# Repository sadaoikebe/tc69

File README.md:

# TC69 静電容量親指シフト 65% キーボード

## 特徴

オープンソースの親指シフトキーボードです。

* 静電容量式
* QMK対応
* JLCPCBで作成したPCB
* 3Dプリントしたケース

## キーボード配列

* ANSI配列ベース
* 矢印キーあり
* 対応する親指シフトファームウェア [tc69 firmware](https://github.com/sadaoikebe/qmk_firmware/tree/capacitive)
* 親指シフト対応、親指キーB下割れ
* 親指キーに3u/2.75uのキーキャップを使用

<!--
["Esc\n\n~\n`","!\n1","@\n2","#\n3","$\n4","%\n5","^\n6","&\n7","*\n8","(\n9",")\n0","_\n-","+\n=",{w:2},"Backspace","Home"],
[{w:1.5},"Tab","Q","W","E","R","T","Y","U","I","O","P","{\n[","}\n]",{w:1.5},"|\n\\","PgUp"],
[{w:1.75},"Ctrl","A","S","D","F","G","H","J","K","L",":\n;","\"\n'",{w:2.25},"Enter","PgUp"],
[{w:2.25},"Shift","Z","X","C","V","B","N","M","<\n,",">\n.","?\n/",{w:1.75},"Shift","Up","End"],
[{a:7,w:1.25},"",{w:1.25},"",{w:1.25},"",{w:3},"3u 左親指",{w:2.75},"2.75u 右親指",{w:1.25},"",{w:1.25},"","","","",""],
-->

静電容量キーボードなので配列は固定で変えられません

# BOM

Item |ソース | 数量 |  備考
:--- | :--- | :--- | :---
TC69 PCBA | [JLCPCB PCBA](pcb/) | 1 |
オペアンプ AD8601ARTZ | AliEx/淘宝等 | 1 |
ロジック 74AHC1G04 | AliEx/淘宝等 | 1 |
ケース | [3D Printed](case/) | 1 | 
定位板 | [Laser Cut Brass](plate/) | 1 | t=1.5mm アクリルでも良いが割れやすい
ヒートセット M3x6mmx4.6mm | [AliEx/淘宝等](https://www.aliexpress.com/item/1005002288716120.html) | 8 | 長さは6mmでなくても良い
M3 円頭六角ボルト 6mm | | 8 |  
M2 低頭精密小ねじ M2*8mm FX-0280EB | [Wilco](https://wilco.jp/products/F/FX-EB.html#page3) | 12 |
クッション 2mm厚 x 60mm x 4mm | | 16 | Poron/EVAフォーム等
Seeed Xiao RP2040 | [Seeed Studio](https://www.seeedstudio.com/XIAO-RP2040-v1-0-p-5026.html) | 1 | 
NiZ プランジャーキット | [NiZ](https://www.nizkeyboard.com/products/2019-new-niz-ec-switch) | 1セット |
コニカルスプリング | [淘宝](https://item.taobao.com/item.htm?spm=a1z0d.6639537/tb.1997196601.4.194d74840XCdqh&id=616137021034) | 69 |
シリコンドーム | [NiZ](https://www.nizkeyboard.com/products/ec-silicone-domes-35g-45g-55g) | 1セット |
2u スタビライザー | AliEx/淘宝/自キ専門店等 | 5 | Plate Mount
3u スタビライザー | AliEx/淘宝/自キ専門店等 | 1 | Plate Mount
キーキャップ | AliEx/淘宝/自キ専門店等 | 1セット | 3u/2.75uの親指キーが必要

## 組み立て工程

1. 定位板はあらかじめM2タップを切る
2. PCBにXiao RP2040, オペアンプ, ロジックIC を取り付け
3. コニカルスプリングを並べてラバードームを乗せる
4. 定位板にハウジングを取り付け、プランジャーを通す
5. 定位板とPCBをM2*8ボルトで緊結する
6. PCBにクッションを貼る
7. ファームウェア書き込み
8. ケースに入れて完成

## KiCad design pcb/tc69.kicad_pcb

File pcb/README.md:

https://www.seeedstudio.com/blog/2020/04/23/use-seeeduino-xiao-in-kicad-pcb-design-like-a-components/

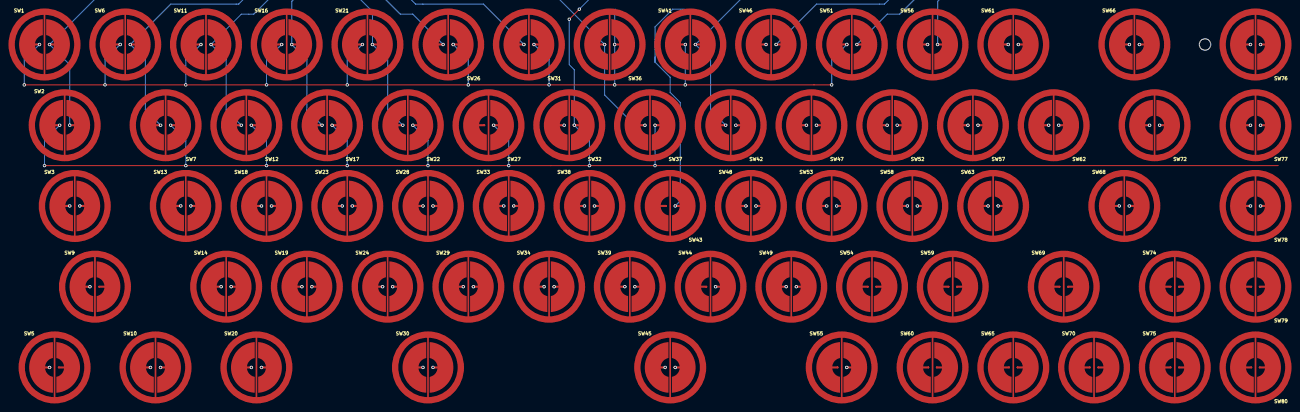
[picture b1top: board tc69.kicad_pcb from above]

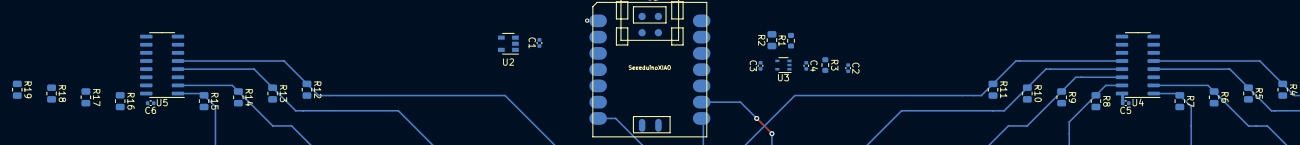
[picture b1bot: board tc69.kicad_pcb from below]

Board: 2 copper layers, 99 parts (30 on the bottom side), 32 nets.

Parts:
C1, C4, C5, C6: 100n; C_0402_1005Metric
C2: 330p; C_0402_1005Metric
C3: 10p; C_0402_1005Metric
R1: 1k; R_0603_1608Metric
R2: 43k; R_0805_2012Metric
R3: 100; R_0603_1608Metric
R4, R5, R6, R7, R8, R9, R10, R11, R12, R13, R14, R15, R16, R17, R18, R19: 100k; R_0805_2012Metric
SW1: ESC; ecs_pad
SW2: TAB; ecs_pad
SW3: CAPS; ecs_pad
SW5: LCTRL; ecs_pad
SW6: 1; ecs_pad
SW7: Q; ecs_pad
SW9: LSHFT; ecs_pad
SW10: LWIN; ecs_pad
SW11: 2; ecs_pad
SW12: W; ecs_pad
SW13: A; ecs_pad
SW14: Z; ecs_pad
SW16: 3; ecs_pad
SW17: E; ecs_pad
SW18: S; ecs_pad
SW19: X; ecs_pad
SW20: LALT; ecs_pad
SW21: 4; ecs_pad
SW22: R; ecs_pad
SW23: D; ecs_pad
SW24: C; ecs_pad
SW26: 5; ecs_pad
SW27: T; ecs_pad
SW28: F; ecs_pad
SW29: V; ecs_pad
SW30: LSPC; ecs_pad
SW31: 6; ecs_pad
SW32: Y; ecs_pad
SW33: G; ecs_pad
SW34: B; ecs_pad
SW36: 7; ecs_pad
SW37: U; ecs_pad
SW38: H; ecs_pad
SW39: N; ecs_pad
SW41: 8; ecs_pad
SW42: I; ecs_pad
SW43: J; ecs_pad
SW44: M; ecs_pad
SW45: RSPC; ecs_pad
SW46: 9; ecs_pad
SW47: O; ecs_pad
SW48: K; ecs_pad
SW49: COMMA; ecs_pad
SW51: 0; ecs_pad
SW52: P; ecs_pad
SW53: L; ecs_pad
SW54: DOT; ecs_pad
SW55: RALT; ecs_pad
SW56: MINUS; ecs_pad
SW57: LBRC; ecs_pad
SW58: SCLN; ecs_pad
SW59: SLSH; ecs_pad
SW60: RWIN; ecs_pad
SW61: EQUAL; ecs_pad
SW62: RBRC; ecs_pad
SW63: QUOTE; ecs_pad
SW65: APP; ecs_pad
SW66: BS; ecs_pad
SW68: ENTER; ecs_pad
SW69: RSHFT; ecs_pad
SW70: LEFT; ecs_pad
SW72: BSLSH; ecs_pad
SW74: UP; ecs_pad
SW75: DOWN; ecs_pad
SW76: HOME; ecs_pad
SW77: PGUP; ecs_pad
SW78: PGDN; ecs_pad
SW79: END; ecs_pad
SW80: RIGHT; ecs_pad
U1: SeeeduinoXIAO; Seeeduino XIAO-MOUDLE14P-2.54-21X17.8MM
U2: 74AHC1G04; SOT-23-5
U3: TLV9051; SOT-353_SC-70-5
U4, U5: 4051; SOIC-16_3.9x9.9mm_P1.27mm

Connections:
+5V: C1.2, C4.2, C5.2, C6.2, U1.14, U2.5, U3.5, U4.16, U5.16
ADC: C3.1, R2.1, U1.11, U3.4
GND: C1.1, C2.2, C4.1, C5.1, C6.1, R1.2, R4.2, R5.2, R6.2, R7.2, R8.2, R9.2, R10.2, R11.2, R12.2, R13.2, R14.2, R15.2, R16.2, R17.2, R18.2, R19.2, SW1.3, SW2.3, SW3.3, SW5.3, SW6.3, SW7.3, SW9.3, SW10.3, SW11.3, SW12.3, SW13.3, SW14.3, SW16.3, SW17.3, SW18.3, SW19.3, SW20.3, SW21.3, SW22.3, SW23.3, SW24.3, SW26.3, SW27.3, SW28.3, SW29.3, SW30.3, SW31.3, SW32.3, SW33.3, SW34.3, SW36.3, SW37.3, SW38.3, SW39.3, SW41.3, SW42.3, SW43.3, SW44.3, SW45.3, SW46.3, SW47.3, SW48.3, SW49.3, SW51.3, SW52.3, SW53.3, SW54.3, SW55.3, SW56.3, SW57.3, SW58.3, SW59.3, SW60.3, SW61.3, SW62.3, SW63.3, SW65.3, SW66.3, SW68.3, SW69.3, SW70.3, SW72.3, SW74.3, SW75.3, SW76.3, SW77.3, SW78.3, SW79.3, SW80.3, U1.13, U2.3, U3.2, U4.7, U4.8, U5.7, U5.8
IS0: U2.4, U5.6
unnamed: C3.2, R1.1, R2.2, U3.3
unnamed: R3.1, U3.1
S0: U1.1, U2.2, U4.6
S1: U1.2, U4.11, U5.11
S2: U1.3, U4.10, U5.10
S3: U1.4, U4.9, U5.9
SENSE: C2.1, R3.2, U1.10, U4.3, U5.3
col1: R4.1, SW1.2, SW2.2, SW3.2, SW5.2, U4.5
col2: R5.1, SW6.2, SW7.2, SW9.2, SW10.2, U4.4
col3: R6.1, SW11.2, SW12.2, SW13.2, SW14.2, U4.2
col4: R7.1, SW16.2, SW17.2, SW18.2, SW19.2, SW20.2, U4.1
col5: R8.1, SW21.2, SW22.2, SW23.2, SW24.2, U4.15
col6: R9.1, SW26.2, SW27.2, SW28.2, SW29.2, SW30.2, U4.14
col7: R10.1, SW31.2, SW32.2, SW33.2, SW34.2, U4.13
col8: R11.1, SW36.2, SW37.2, SW38.2, SW39.2, U4.12
col9: R12.1, SW41.2, SW42.2, SW43.2, SW44.2, SW45.2, U5.5
col10: R13.1, SW46.2, SW47.2, SW48.2, SW49.2, U5.4
col11: R14.1, SW51.2, SW52.2, SW53.2, SW54.2, SW55.2, U5.2
col12: R15.1, SW56.2, SW57.2, SW58.2, SW59.2, SW60.2, U5.1
col13: R16.1, SW61.2, SW62.2, SW63.2, SW65.2, U5.15
col14: R17.1, SW66.2, SW68.2, SW69.2, SW70.2, U5.14
col15: R18.1, SW72.2, SW74.2, SW75.2, U5.13
col16: R19.1, SW76.2, SW77.2, SW78.2, SW79.2, SW80.2, U5.12
row1: SW1.1, SW6.1, SW11.1, SW16.1, SW21.1, SW26.1, SW31.1, SW36.1, SW41.1, SW46.1, SW51.1, SW56.1, SW61.1, SW66.1, SW76.1, U1.8
row2: SW2.1, SW7.1, SW12.1, SW17.1, SW22.1, SW27.1, SW32.1, SW37.1, SW42.1, SW47.1, SW52.1, SW57.1, SW62.1, SW72.1, SW77.1, U1.9
row3: SW3.1, SW13.1, SW18.1, SW23.1, SW28.1, SW33.1, SW38.1, SW43.1, SW48.1, SW53.1, SW58.1, SW63.1, SW68.1, SW78.1, U1.7
row4: SW9.1, SW14.1, SW19.1, SW24.1, SW29.1, SW34.1, SW39.1, SW44.1, SW49.1, SW54.1, SW59.1, SW69.1, SW74.1, SW79.1, U1.6
row5: SW5.1, SW10.1, SW20.1, SW30.1, SW45.1, SW55.1, SW60.1, SW65.1, SW70.1, SW75.1, SW80.1, U1.5

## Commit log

2021-11-17 partly routed
2021-11-18 wire a bit
2021-11-18 switch wired
2021-11-18 adjust wire
2021-11-19 wire complete
2021-11-19 comment
2021-11-21 handsolder pad
2021-11-22 gnd plane
2021-11-22 trace adjust
2021-11-23 route
2021-11-23 added hole and plate
2021-11-23 library pointer
2022-01-10 evaluation program
2022-01-11 matrix scan and debounce
2022-01-11 working as normal keyboard
2022-01-11 nicola compile
2022-01-11 completekeyboard
2022-01-11 too sensitive
2022-01-11 adjust
2022-01-11 fix power line, made xiao rp2040 compatible
2022-01-12 debounce to ADC hysteresis
2022-01-12 purge time tuning with oscilloscope
2022-01-12 layer action fixedc
2022-01-24 tuning
2022-01-24 fix op-amp output
2022-03-23 add freecad model
2022-04-08 jlcpcb r2
2022-04-08 case and plate ongoing
2022-04-08 buildable firmware placeholder
2022-04-20 holes for 2u and 3u
2022-05-02 pcb re-wired
2022-05-02 roundtracks and teardrops
2022-05-02 add round case
2022-05-05 plate finished
2022-05-20 add footprint
2022-05-20 modify pad dimension
2022-05-20 add keepout on F_Cu
2022-05-20 change silkscreen; jlcpcb r3.1 ...
2022-05-21 changed pad shape
2022-05-24 increase angle
2022-05-25 dimension
2022-05-28 library path
2022-09-28 revert to the rp2040 version
2022-09-28 rotate 4051
2023-01-02 case rev3 with sensitivity tweak
2023-03-28 add tester
2023-03-28 add readm
2023-03-28 Create LICENSE
2023-07-05 74ahc is a logic not mux
